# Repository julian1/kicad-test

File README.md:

# schematic sheets are symbolically linked into the projects
ln -sf $(pwd)/sheets/adc.sch  ./projects/smu/

# to open a project
kicad projects/dw232/main.pro

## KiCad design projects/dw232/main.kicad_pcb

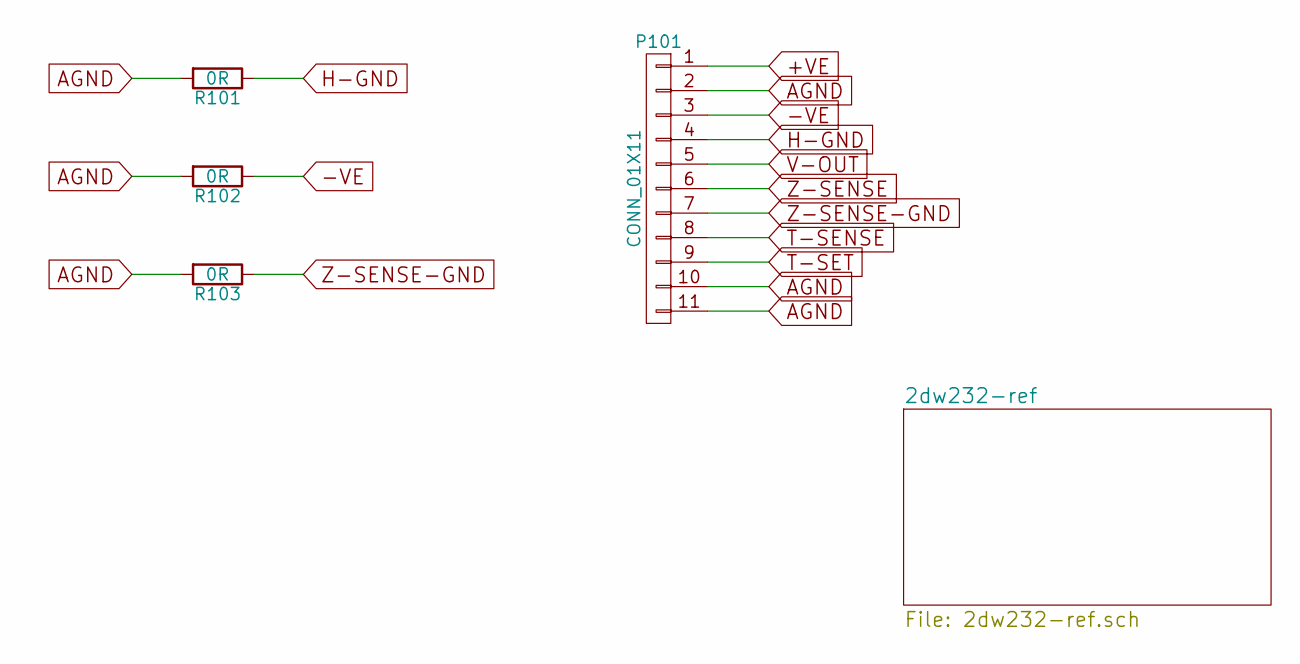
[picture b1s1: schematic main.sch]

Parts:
P101: CONN_01X11; Pin_Header_Straight_1x11
R101, R102, R103: 0R; R_1206

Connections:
+VE: P101.1; also elsewhere on the board
-VE: P101.3, R102.1; also elsewhere on the board
AGND: P101.2, P101.10, P101.11, R101.2, R102.2, R103.2; also elsewhere on the board
H-GND: P101.4, R101.1; also elsewhere on the board
T-SENSE: P101.8; also elsewhere on the board
T-SET: P101.9; also elsewhere on the board
V-OUT: P101.5; also elsewhere on the board
Z-SENSE: P101.6; also elsewhere on the board
Z-SENSE-GND: P101.7, R103.1; also elsewhere on the board

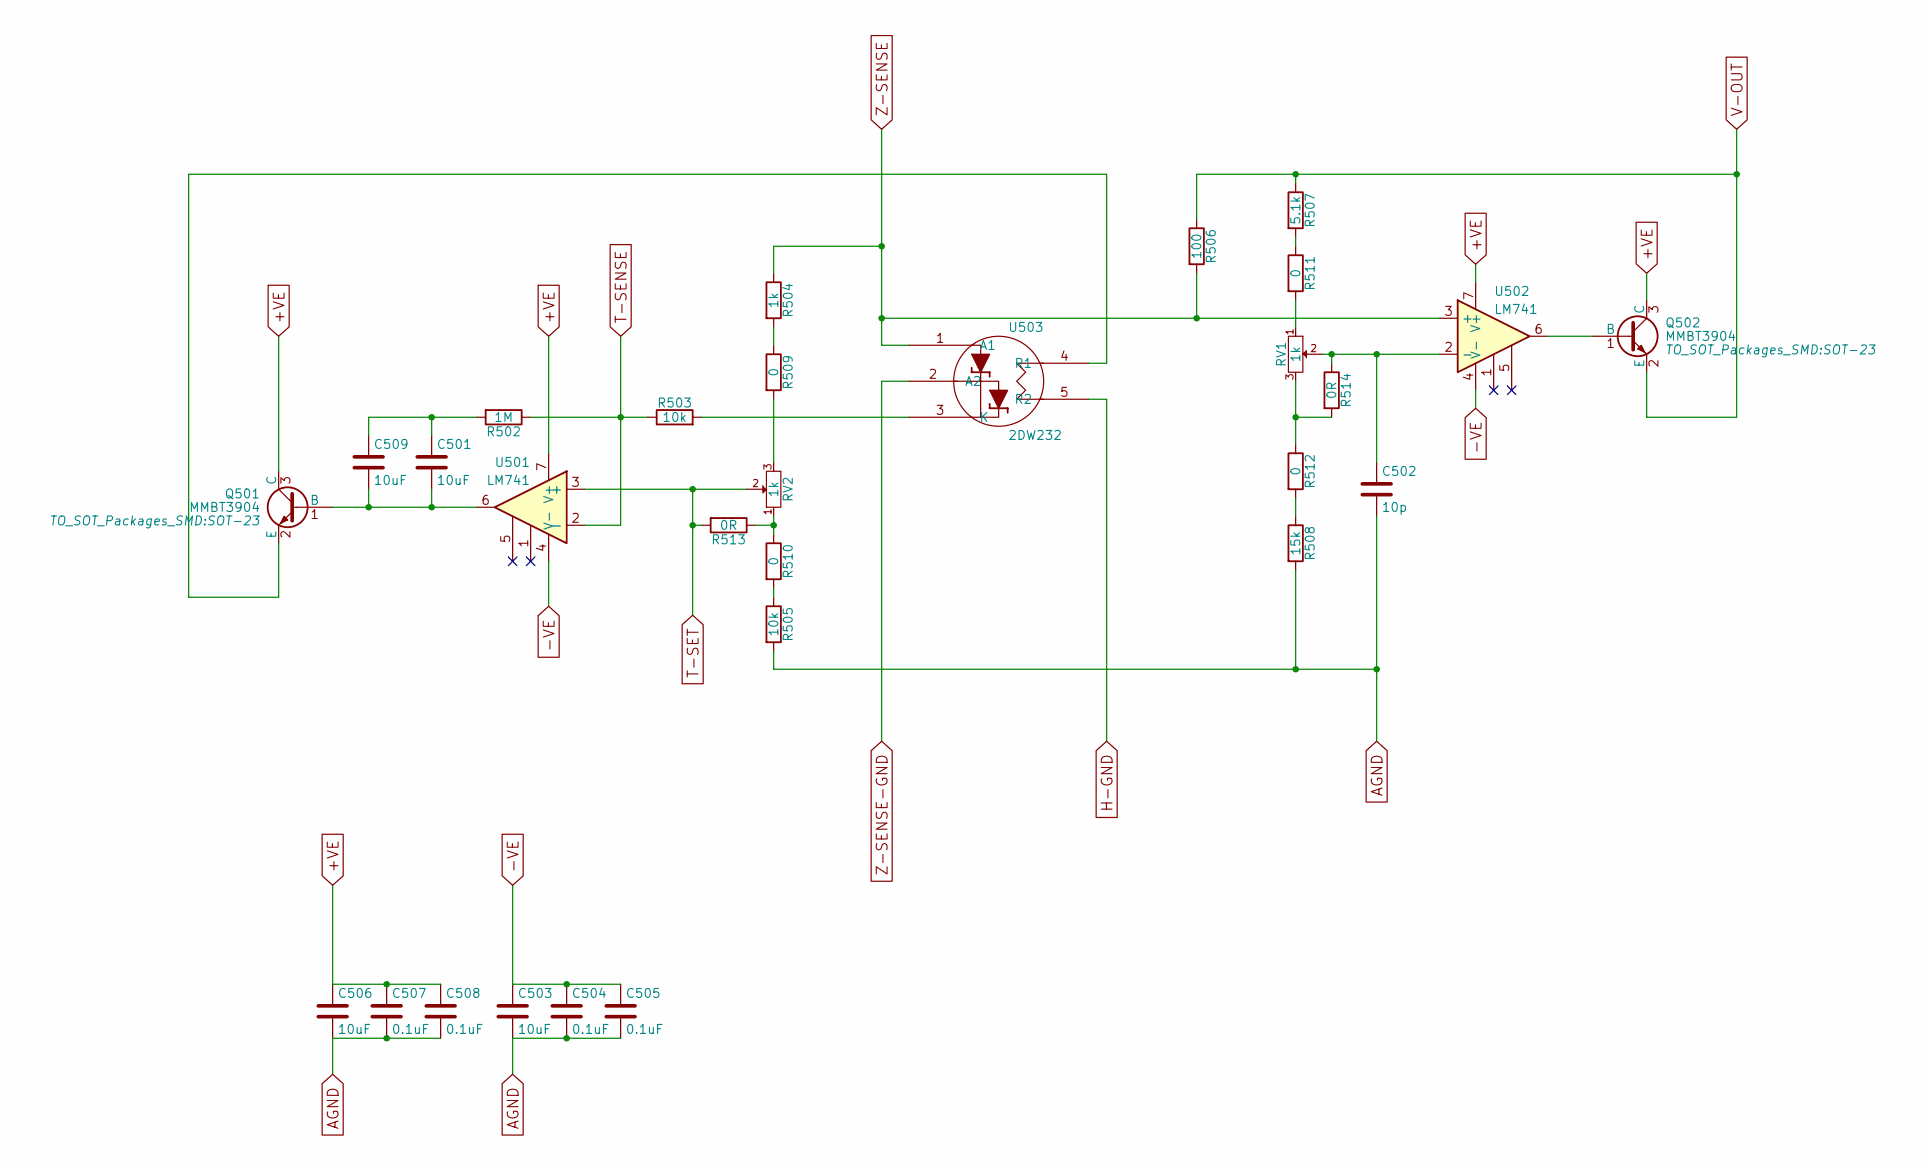
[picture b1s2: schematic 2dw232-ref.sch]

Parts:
C501, C503, C506, C509: 10uF; C_1206
C502: 10p; C_1206
C504, C505, C507, C508: 0.1uF; C_1206
Q501, Q502: MMBT3904; SOT-23
R502: 1M; R_1206
R503: 10k; R_1206
R504: 1k; Resistor_TO-220_Vertical
R505: 10k; Resistor_TO-220_Vertical
R506: 100; Resistor_TO-220_Vertical
R507: 5.1k; Resistor_TO-220_Vertical
R508: 15k; Resistor_TO-220_Vertical
R509, R510, R511, R512: 0; Resistor_TO-220_Vertical
R513, R514: 0R; R_1206
RV1, RV2: 1k; Potentiometer_Bourns_3296W_3-8Zoll_Inline_ScrewUp
U501, U502: LM741; SOIC-8_3.9x4.9mm_Pitch1.27mm
U503: 2DW232; TO-5_Housing_2DW232_5Pin

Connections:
+VE: C506.1, C507.1, C508.1, Q501.3 (C), Q502.3 (C), U501.7 (V+), U502.7 (V+); also elsewhere on the board
-VE: C503.1, C504.1, C505.1, U501.4 (V-), U502.4 (V-); also elsewhere on the board
AGND: C502.2, C503.2, C504.2, C505.2, C506.2, C507.2, C508.2, R505.2, R508.2; also elsewhere on the board
H-GND: U503.5 (R2); also elsewhere on the board
unnamed: C501.1, C509.1, R502.2
unnamed: C501.2, C509.2, Q501.1 (B), U501.6
unnamed: C502.1, R514.1, RV1.2, U502.2 (-)
unnamed: Q501.2 (E), U503.4 (R1)
unnamed: Q502.1 (B), U502.6
unnamed: R503.2, U503.3 (K)
unnamed: R504.2, R509.1
unnamed: R505.1, R510.2
unnamed: R507.2, R511.1
unnamed: R508.1, R512.2
unnamed: R509.2, RV2.3
unnamed: R510.1, R513.1, RV2.1
unnamed: R511.2, RV1.1
unnamed: R512.1, R514.2, RV1.3
T-SENSE: R502.1, R503.1, U501.2 (-); also elsewhere on the board
T-SET: R513.2, RV2.2, U501.3 (+); also elsewhere on the board
V-OUT: Q502.2 (E), R506.1, R507.1; also elsewhere on the board
Z-SENSE: R504.1, R506.2, U502.3 (+), U503.1 (A1); also elsewhere on the board
Z-SENSE-GND: U503.2 (A2); also elsewhere on the board

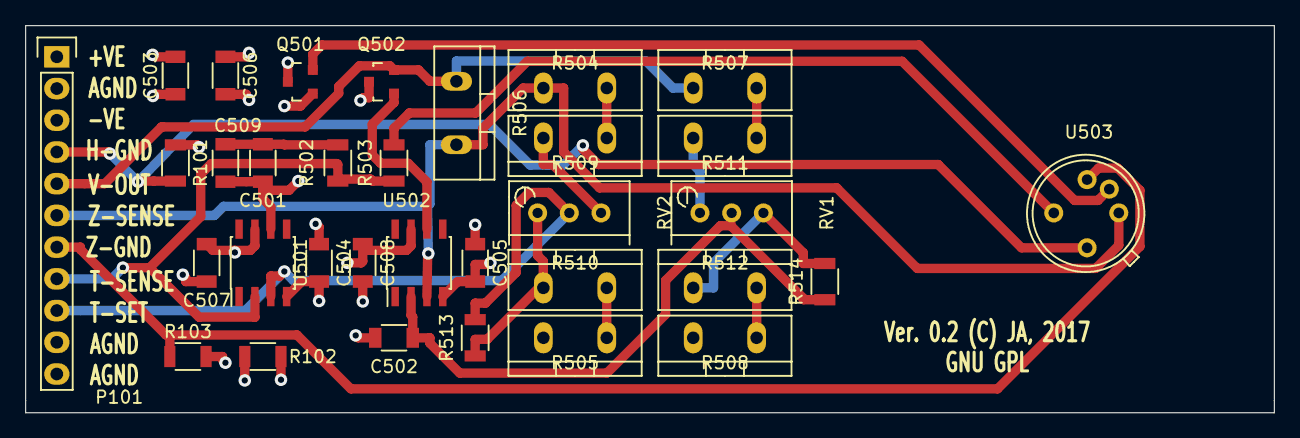
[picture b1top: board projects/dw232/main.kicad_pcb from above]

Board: 4 copper layers, 100.0 x 31.0 mm, 33 parts (0 on the bottom side), 23 nets.

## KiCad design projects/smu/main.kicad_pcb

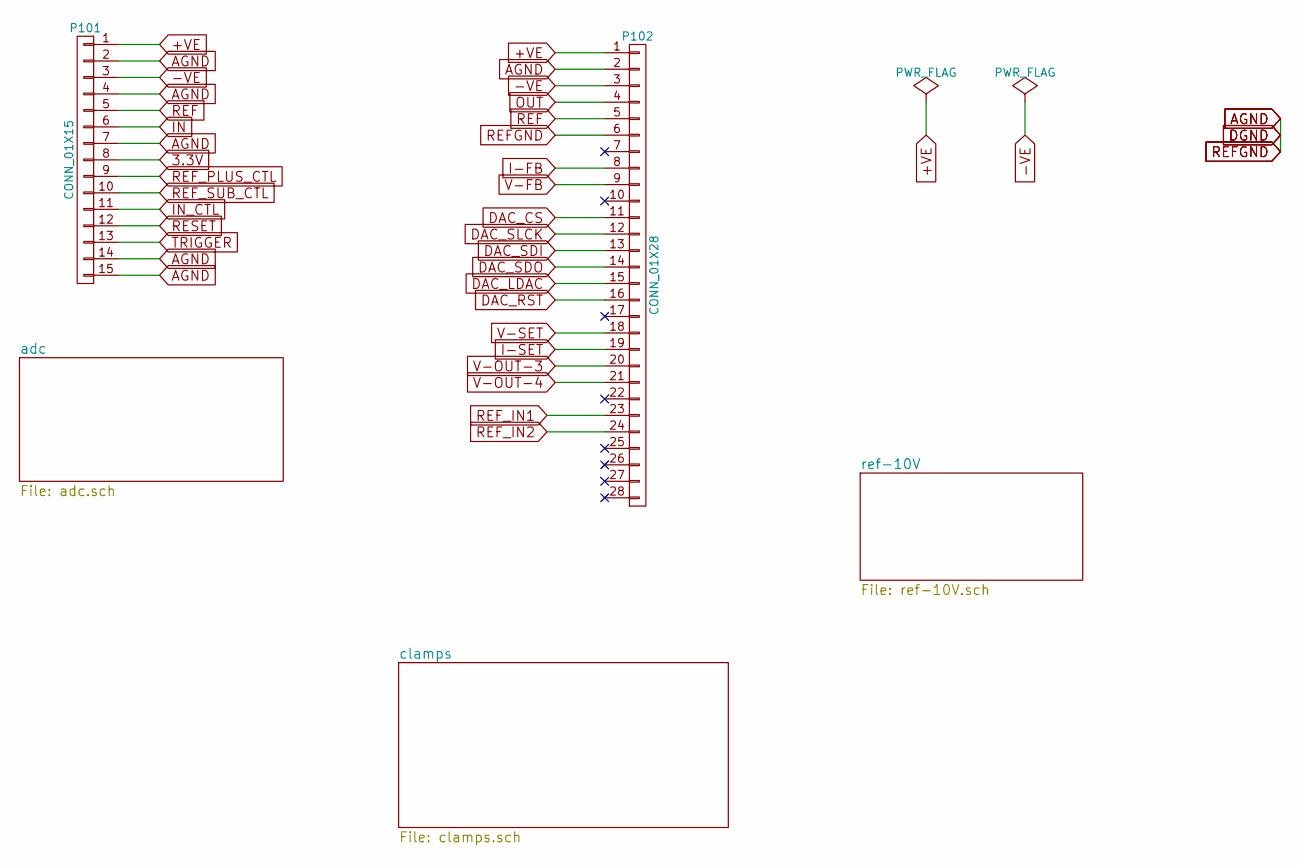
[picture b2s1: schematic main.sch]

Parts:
P101: CONN_01X15; Pin_Header_Straight_1x15
P102: CONN_01X28; Pin_Header_Straight_1x28

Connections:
3.3V: P101.8; also elsewhere on the board
+VE: P101.1, P102.1; also elsewhere on the board
-VE: P101.3, P102.3; also elsewhere on the board
AGND: P101.2, P101.4, P101.7, P101.14, P101.15, P102.2, P102.6; also elsewhere on the board
DAC_CS: P102.11; also elsewhere on the board
DAC_LDAC: P102.15; also elsewhere on the board
DAC_RST: P102.16; also elsewhere on the board
DAC_SDI: P102.13; also elsewhere on the board
DAC_SDO: P102.14; also elsewhere on the board
DAC_SLCK: P102.12; also elsewhere on the board
I-FB: P102.8; also elsewhere on the board
I-SET: P102.19; also elsewhere on the board
IN: P101.6; also elsewhere on the board
IN_CTL: P101.11; also elsewhere on the board
OUT: P102.4; also elsewhere on the board
REF: P101.5, P102.5; also elsewhere on the board
REF_IN1: P102.23; also elsewhere on the board
REF_IN2: P102.24; also elsewhere on the board
REF_PLUS_CTL: P101.9; also elsewhere on the board
REF_SUB_CTL: P101.10; also elsewhere on the board
RESET: P101.12; also elsewhere on the board
TRIGGER: P101.13; also elsewhere on the board
V-FB: P102.9; also elsewhere on the board
V-OUT-3: P102.20; also elsewhere on the board
V-OUT-4: P102.21; also elsewhere on the board
V-SET: P102.18; also elsewhere on the board

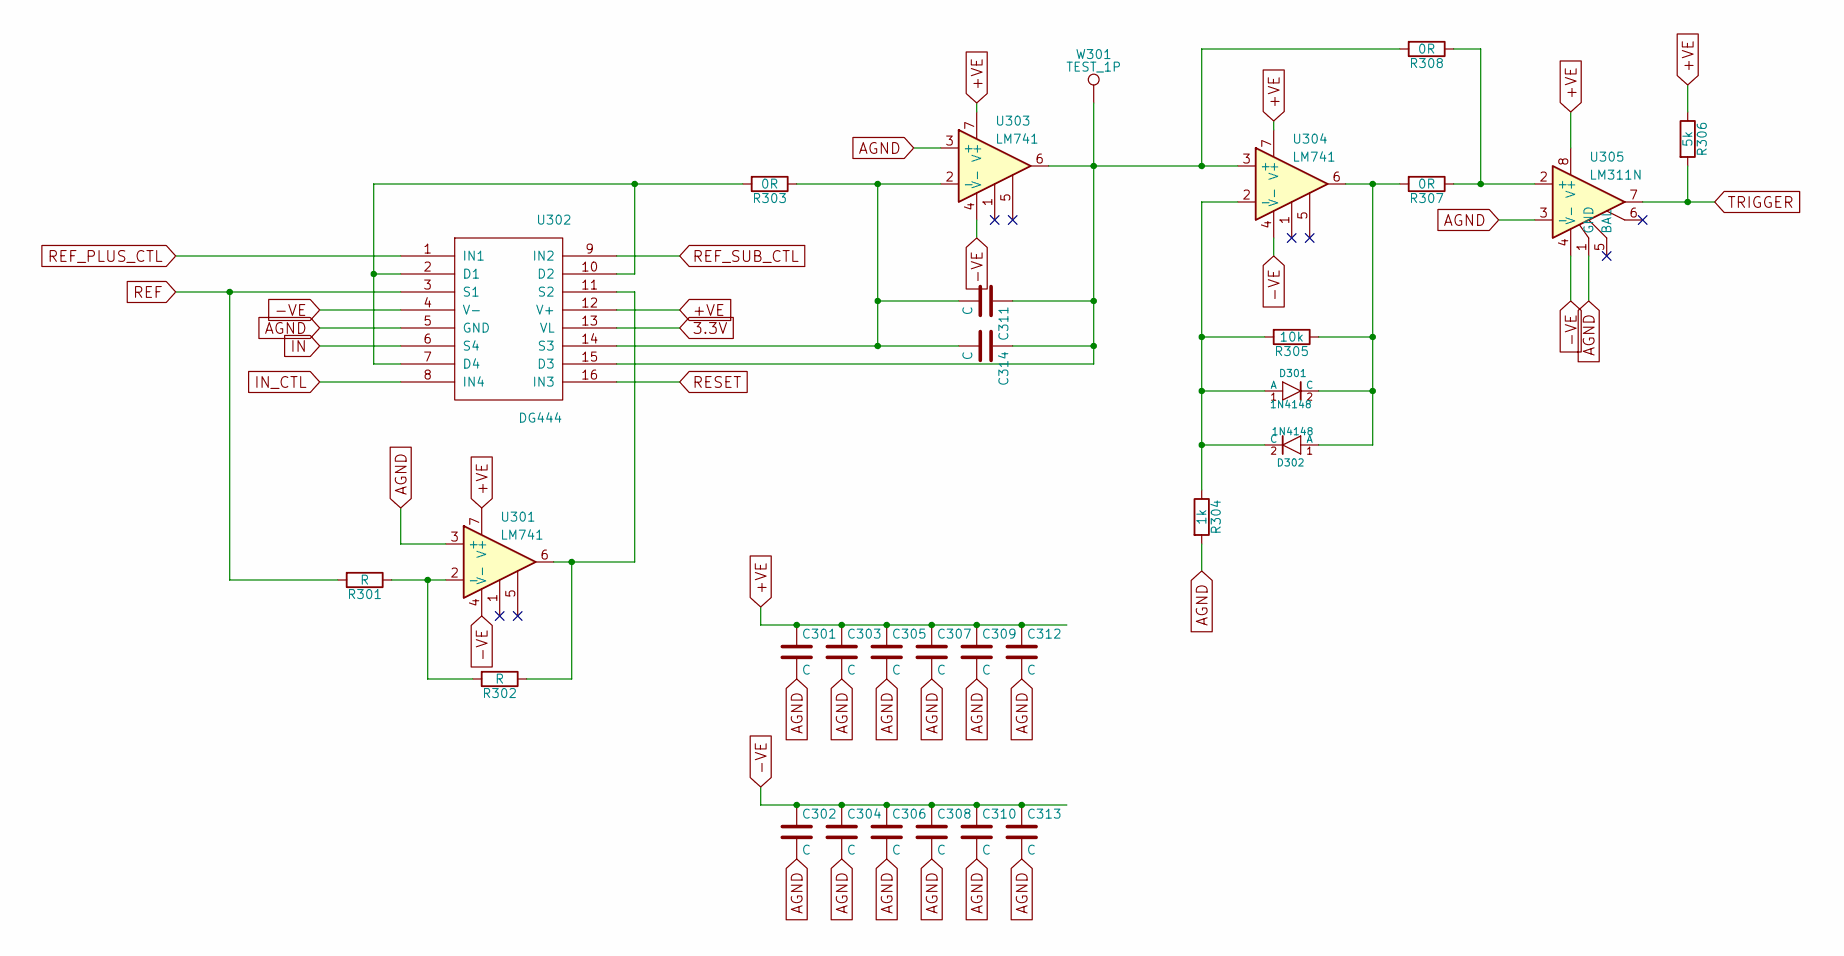
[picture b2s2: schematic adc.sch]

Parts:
C301, C302, C303, C304, C305, C306, C307, C308, C309, C310, C311, C312, C313: C; C_1206
C314: C; C_Rect_L7_W3.5_P5
D301, D302: 1N4148; MiniMELF_Standard
R16, R307, R308: 0R; R_1206
R301, R302: R; R_1206
R304: 1k; R_1206
R305: 10k; R_1206
R306: 5k; R_1206
U8: DG444; SOIC-16_3.9x9.9mm_Pitch1.27mm
U9, U301, U304: LM741; SOIC-8_3.9x4.9mm_Pitch1.27mm
U305: LM311N; SOIC-8_3.9x4.9mm_Pitch1.27mm
W301: TEST_1P; Pin_Header_Straight_1x01

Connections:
+VE: C301.1, C303.1, C305.1, C307.1, C309.1, C312.1, R306.1, U301.7 (V+), U304.7 (V+), U305.8 (V+); also elsewhere on the board
-VE: C302.1, C304.1, C306.1, C308.1, C310.1, C313.1, U301.4 (V-), U304.4 (V-), U305.4 (V-); also elsewhere on the board
AGND: C301.2, C302.2, C303.2, C304.2, C305.2, C306.2, C307.2, C308.2, C309.2, C310.2, C312.2, C313.2, R304.2, U301.3 (+), U305.1 (GND), U305.3 (-); also elsewhere on the board
unnamed 14: C311.1, C314.1, R308.2, U304.3 (+), W301.1; also elsewhere on the board
unnamed 15: C311.2, C314.2; also elsewhere on the board
unnamed: D301.1 (A), D302.2 (C), R304.1, R305.2, U304.2 (-)
unnamed: D301.2 (C), D302.1 (A), R305.1, R307.2, U304.6
unnamed: R301.1, R302.2, U301.2 (-)
unnamed 23: R302.1, U301.6; also elsewhere on the board
unnamed: R307.1, R308.1, U305.2 (+)
REF: R301.2; also elsewhere on the board
TRIGGER: R306.2, U305.7; also elsewhere on the board

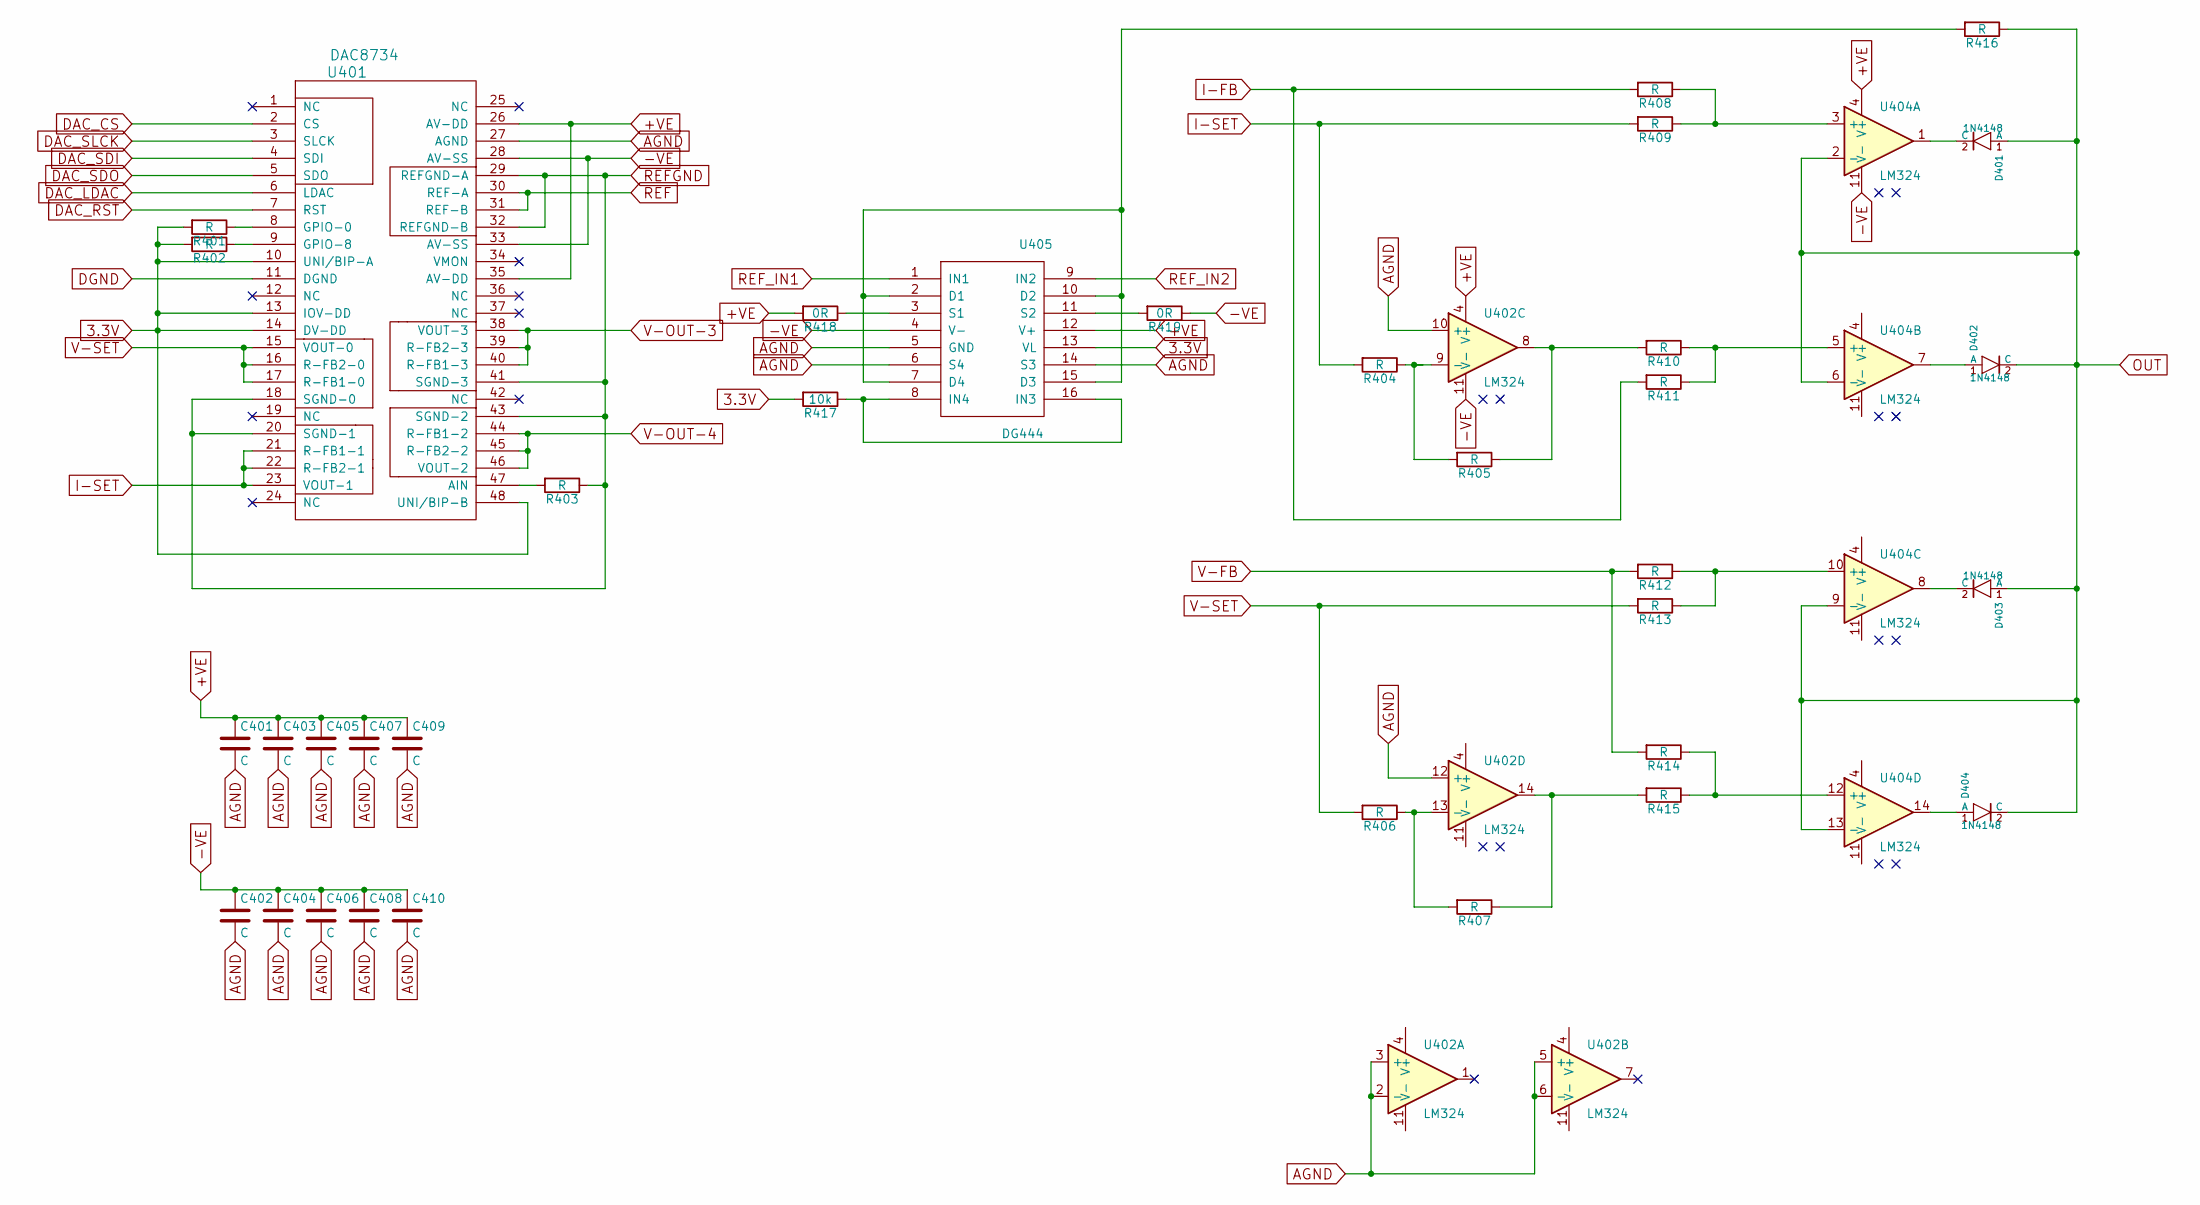
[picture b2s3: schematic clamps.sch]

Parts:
C401, C402, C403, C404, C405, C406, C407, C408, C409, C410: C; C_1206
D401, D402, D403, D404: 1N4148; MiniMELF_Standard
R401, R402, R403, R404, R405, R406, R407, R408, R409, R410, R411, R412, R413, R414, R415, R416: R; R_1206
R417: 10k; R_1206
R418, R419: 0R; R_1206
U401: DAC8734; TQFP-48_7x7mm_Pitch0.5mm
U402, U404: LM324; SOIC-14_3.9x8.7mm_Pitch1.27mm
U405: DG444; SOIC-16_3.9x9.9mm_Pitch1.27mm

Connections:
3.3V: R401.2, R402.2, R417.2, U401.10 (UNI/BIP-A), U401.13 (IOV-DD), U401.14 (DV-DD), U401.48 (UNI/BIP-B), U405.13 (VL); also elsewhere on the board
+VE: C401.1, C403.1, C405.1, C407.1, C409.1, R418.2, U401.26 (AV-DD), U401.35 (AV-DD), U402.4 (V+), U404.4 (V+), U405.12 (V+); also elsewhere on the board
-VE: C402.1, C404.1, C406.1, C408.1, C410.1, R419.1, U401.28 (AV-SS), U401.33 (AV-SS), U402.11 (V-), U404.11 (V-), U405.4 (V-); also elsewhere on the board
AGND: C401.2, C402.2, C403.2, C404.2, C405.2, C406.2, C407.2, C408.2, C409.2, C410.2, R403.1, U401.11 (DGND), U401.18 (SGND-0), U401.20 (SGND-1), U401.27 (AGND), U401.29 (REFGND-A), U401.32 (REFGND-B), U401.41 (SGND-3), U401.43 (SGND-2), U402.2 (-), U402.3 (+), U402.5 (+), U402.6 (-), U402.10 (+), U402.12 (+), U405.5 (GND), U405.6 (S4), U405.14 (S3); also elsewhere on the board
DAC_CS: U401.2 (CS); also elsewhere on the board
DAC_LDAC: U401.6 (LDAC); also elsewhere on the board
DAC_RST: U401.7 (RST); also elsewhere on the board
DAC_SDI: U401.4 (SDI); also elsewhere on the board
DAC_SDO: U401.5 (SDO); also elsewhere on the board
DAC_SLCK: U401.3 (SLCK); also elsewhere on the board
I-FB: R408.2, R411.2; also elsewhere on the board
I-SET: R404.2, R409.2, U401.21 (R-FB1-1), U401.22 (R-FB2-1), U401.23 (VOUT-1); also elsewhere on the board
unnamed: D401.2 (C), U404.1
unnamed: D402.1 (A), U404.7
unnamed: D403.2 (C), U404.8
unnamed: D404.1 (A), U404.14
unnamed: R401.1, U401.8 (GPIO-0)
unnamed: R402.1, U401.9 (GPIO-8)
unnamed: R403.2, U401.47 (AIN)
unnamed: R404.1, R405.2, U402.9 (-)
unnamed: R405.1, R410.2, U402.8
unnamed: R406.1, R407.2, U402.13 (-)
unnamed: R407.1, R415.2, U402.14
unnamed: R408.1, R409.1, U404.3 (+)
unnamed: R410.1, R411.1, U404.5 (+)
unnamed: R412.1, R413.1, U404.10 (+)
unnamed: R414.1, R415.1, U404.12 (+)
unnamed: R416.2, U405.2 (D1), U405.7 (D4), U405.10 (D2), U405.15 (D3)
unnamed: R417.1, U405.8 (IN4), U405.16 (IN3)
unnamed 39: R418.1, U405.3 (S1); also elsewhere on the board
unnamed 40: R419.2, U405.11 (S2); also elsewhere on the board
OUT: D401.1 (A), D402.2 (C), D403.1 (A), D404.2 (C), R416.1, U404.2 (-), U404.6 (-), U404.9 (-), U404.13 (-); also elsewhere on the board
REF: U401.30 (REF-A), U401.31 (REF-B); also elsewhere on the board
REF_IN1: U405.1 (IN1); also elsewhere on the board
REF_IN2: U405.9 (IN2); also elsewhere on the board
V-FB: R412.2, R414.2; also elsewhere on the board
V-OUT-3: U401.38 (VOUT-3), U401.39 (R-FB2-3), U401.40 (R-FB1-3); also elsewhere on the board
V-OUT-4: U401.44 (R-FB1-2), U401.45 (R-FB2-2), U401.46 (VOUT-2); also elsewhere on the board
V-SET: R406.2, R413.2, U401.15 (VOUT-0), U401.16 (R-FB2-0), U401.17 (R-FB1-0); also elsewhere on the board

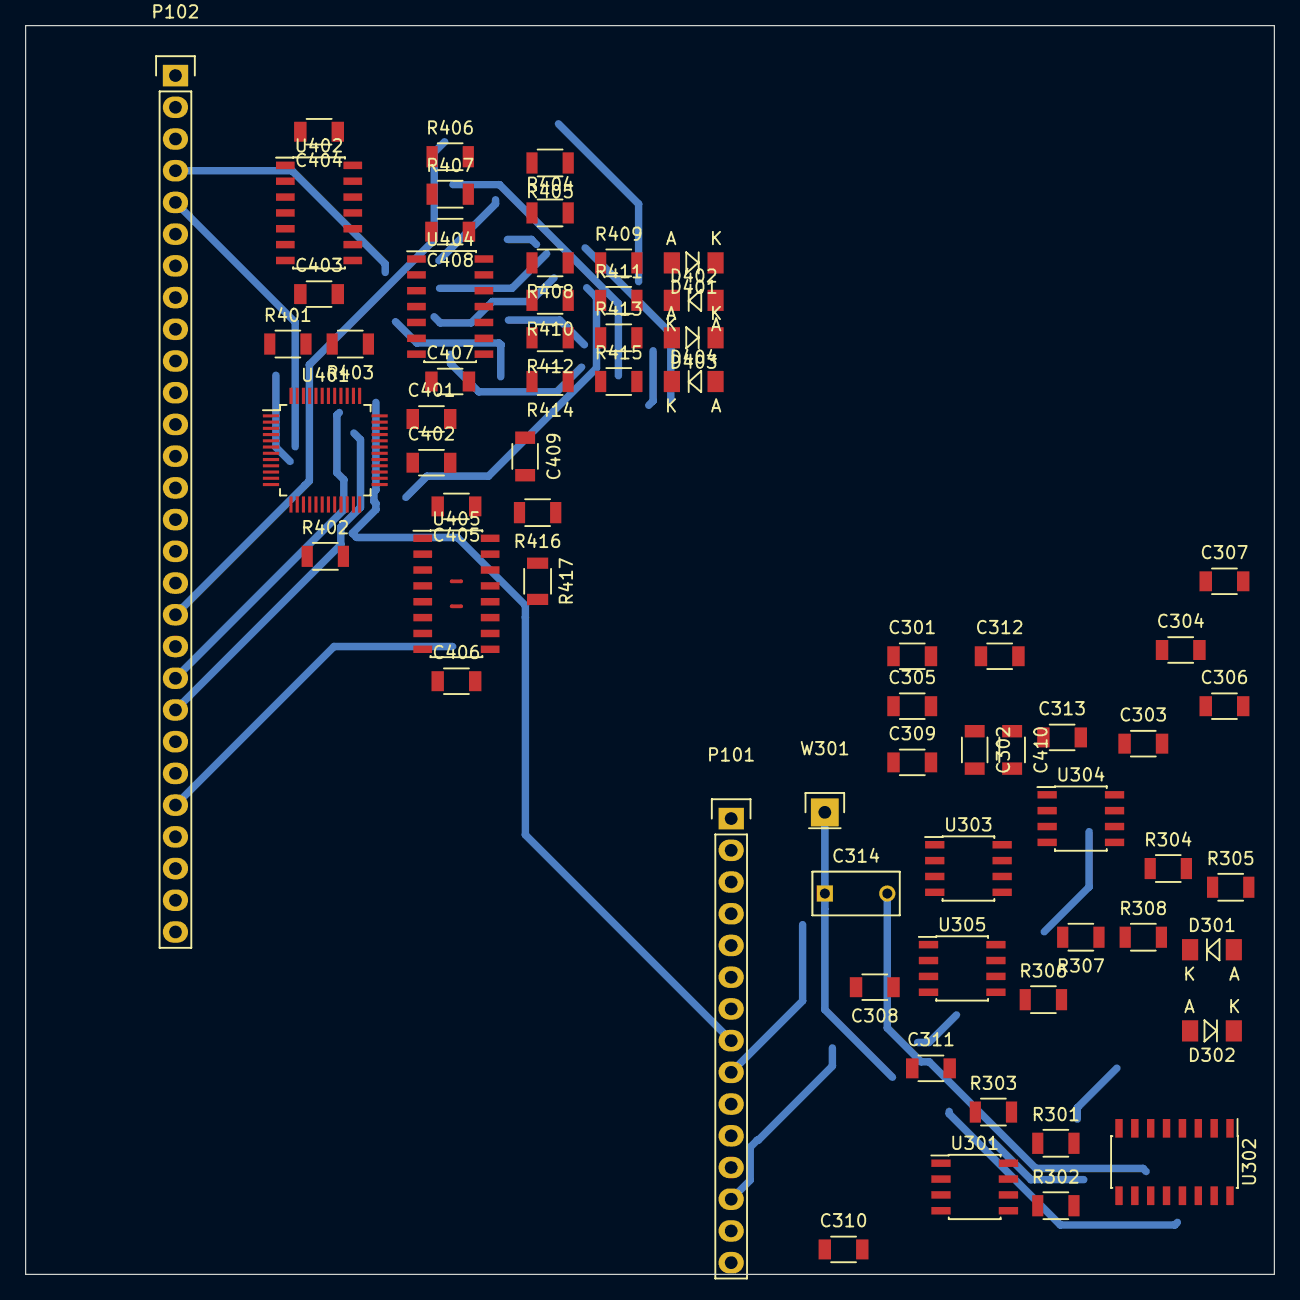
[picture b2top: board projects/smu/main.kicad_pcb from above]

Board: 4 copper layers, 100.0 x 100.0 mm, 69 parts (0 on the bottom side), 53 nets.

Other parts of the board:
R303: 0R; R_1206
U302: DG444; SOIC-16_3.9x9.9mm_Pitch1.27mm
U303: LM741; SOIC-8_3.9x4.9mm_Pitch1.27mm
W401, W402: NET-TIE; NET-TIE-0.3mm

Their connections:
3.3V: U302.13; also elsewhere on the board
+VE: U302.12, U303.7, W401.1; also elsewhere on the board
-VE: U302.4, U303.4, W402.2; also elsewhere on the board
AGND: U302.5, U303.3; also elsewhere on the board
IN: U302.6; also elsewhere on the board
IN_CTL: U302.8; also elsewhere on the board
unnamed 14: U302.15, U303.6; also elsewhere on the board
unnamed 15: R303.1, U302.14, U303.2; also elsewhere on the board
unnamed 23: U302.11; also elsewhere on the board
unnamed: R303.2, U302.2, U302.7, U302.10
unnamed 39: W401.2; also elsewhere on the board
unnamed 40: W402.1; also elsewhere on the board
REF: U302.3; also elsewhere on the board
REF_PLUS_CTL: U302.1; also elsewhere on the board
REF_SUB_CTL: U302.9; also elsewhere on the board
RESET: U302.16; also elsewhere on the board

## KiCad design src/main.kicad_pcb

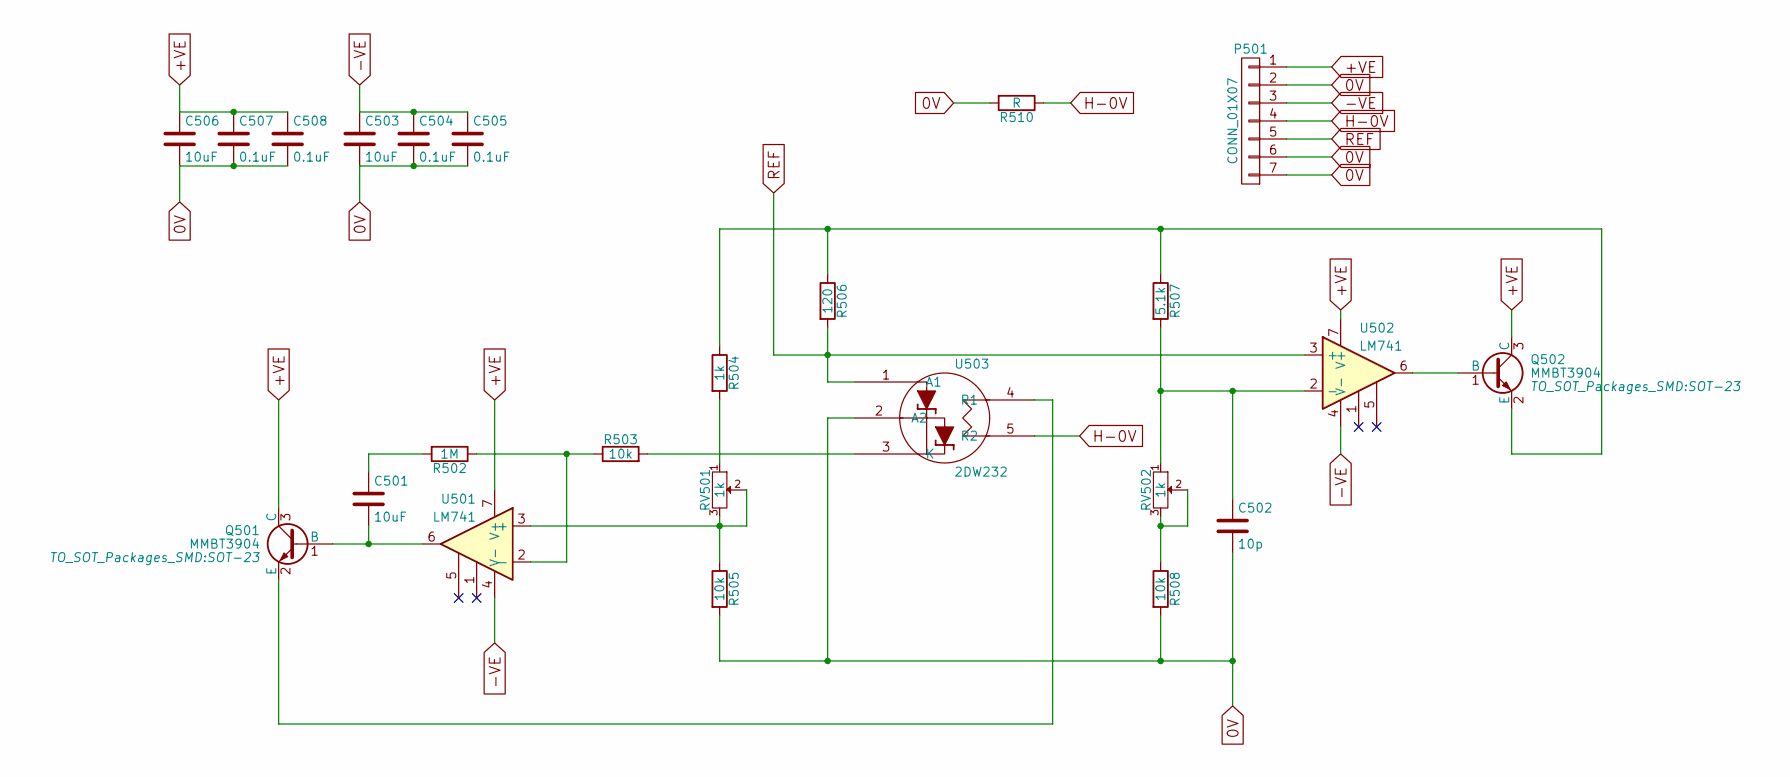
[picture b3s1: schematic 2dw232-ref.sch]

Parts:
C501, C503, C506: 10uF; C_1206
C502: 10p; C_1206
C504, C505, C507, C508: 0.1uF; C_1206
P501: CONN_01X07; Pin_Header_Straight_1x07
Q501, Q502: MMBT3904; SOT-23
R502: 1M; R_1206
R503: 10k; R_1206
R504: 1k; Resistor_TO-220_Vertical
R505, R508: 10k; Resistor_TO-220_Vertical
R506: 120; Resistor_TO-220_Vertical
R507: 5.1k; Resistor_TO-220_Vertical
R510: R; R_1206
RV501, RV502: 1k; Potentiometer_Bourns_3296Y_3-8Zoll_Angular_ScrewUp
U501, U502: LM741; SOIC-8_3.9x4.9mm_Pitch1.27mm
U503: 2DW232; TO-5_Housing_2DW232_5Pin

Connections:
+VE: C506.1, C507.1, C508.1, P501.1, Q501.3 (C), Q502.3 (C), U501.7 (V+), U502.7 (V+); also elsewhere on the board
-VE: C503.1, C504.1, C505.1, P501.3, U501.4 (V-), U502.4 (V-); also elsewhere on the board
H-GND: P501.4, R510.1, U503.5 (R2)
unnamed: C501.1, R502.2
unnamed: C501.2, Q501.1 (B), U501.6
unnamed: C502.1, R507.2, RV502.1, U502.2 (-)
unnamed: Q501.2 (E), U503.4 (R1)
unnamed: Q502.1 (B), U502.6
unnamed: Q502.2 (E), R504.1, R506.1, R507.1
unnamed: R502.1, R503.1, U501.2 (-)
unnamed: R503.2, U503.3 (K)
unnamed: R504.2, RV501.1
unnamed: R505.1, RV501.2, RV501.3, U501.3 (+)
unnamed: R508.1, RV502.2, RV502.3
REF: P501.5, R506.2, U502.3 (+), U503.1 (A1); also elsewhere on the board

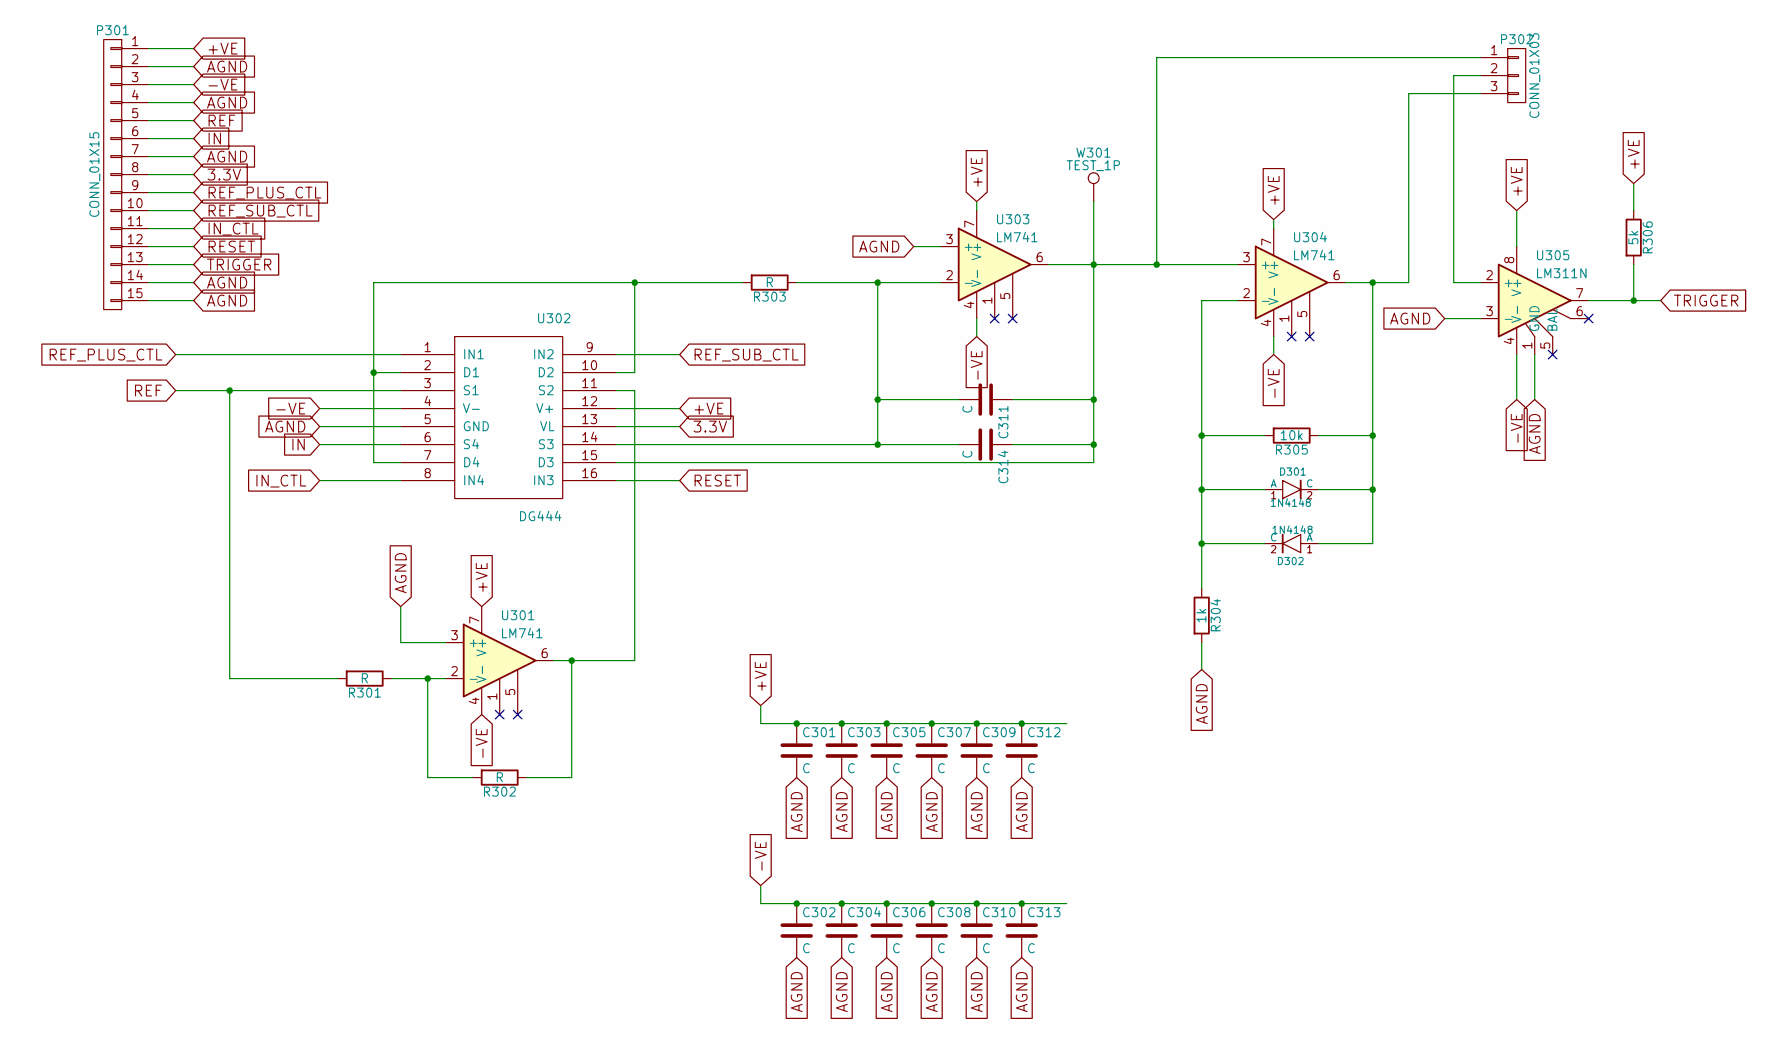
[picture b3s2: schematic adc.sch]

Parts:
C301, C302, C303, C304, C305, C306, C307, C308, C309, C310, C311, C312, C313: C; C_1206
C314: C; C_Rect_L7_W3.5_P5
D301, D302: 1N4148; MiniMELF_Standard
P301: CONN_01X15; Pin_Header_Straight_1x15
P302: CONN_01X03; Pin_Header_Straight_1x03
R16, R301, R302: R; Resistor_TO-220_Vertical
R304: 1k; R_1206
R305: 10k; R_1206
R306: 5k; R_1206
U8: DG444; SOIC-16_3.9x9.9mm_Pitch1.27mm
U9, U301, U304: LM741; SOIC-8_3.9x4.9mm_Pitch1.27mm
U305: LM311N; SOIC-8_3.9x4.9mm_Pitch1.27mm
W301: TEST_1P; Pin_Header_Straight_1x01

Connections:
3.3V: P301.8; also elsewhere on the board
+VE: C301.1, C303.1, C305.1, C307.1, C309.1, C312.1, P301.1, R306.1, U301.7 (V+), U304.7 (V+), U305.8 (V+); also elsewhere on the board
-VE: C302.1, C304.1, C306.1, C308.1, C310.1, C313.1, P301.3, U301.4 (V-), U304.4 (V-), U305.4 (V-); also elsewhere on the board
IN: P301.6; also elsewhere on the board
IN_CTL: P301.11; also elsewhere on the board
unnamed 8: C311.1, C314.1, P302.1, U304.3 (+), W301.1; also elsewhere on the board
unnamed 9: C311.2, C314.2; also elsewhere on the board
unnamed: D301.1 (A), D302.2 (C), R304.1, R305.2, U304.2 (-)
unnamed: D301.2 (C), D302.1 (A), P302.3, R305.1, U304.6
unnamed: P302.2, U305.2 (+)
unnamed: R301.1, R302.2, U301.2 (-)
unnamed 24: R302.1, U301.6; also elsewhere on the board
REF: P301.5, R301.2; also elsewhere on the board
REF_PLUS_CTL: P301.9; also elsewhere on the board
REF_SUB_CTL: P301.10; also elsewhere on the board
RESET: P301.12; also elsewhere on the board
TRIGGER: P301.13, R306.2, U305.7

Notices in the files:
projects/dw232/main.kicad_pcb:
GNU GPL
